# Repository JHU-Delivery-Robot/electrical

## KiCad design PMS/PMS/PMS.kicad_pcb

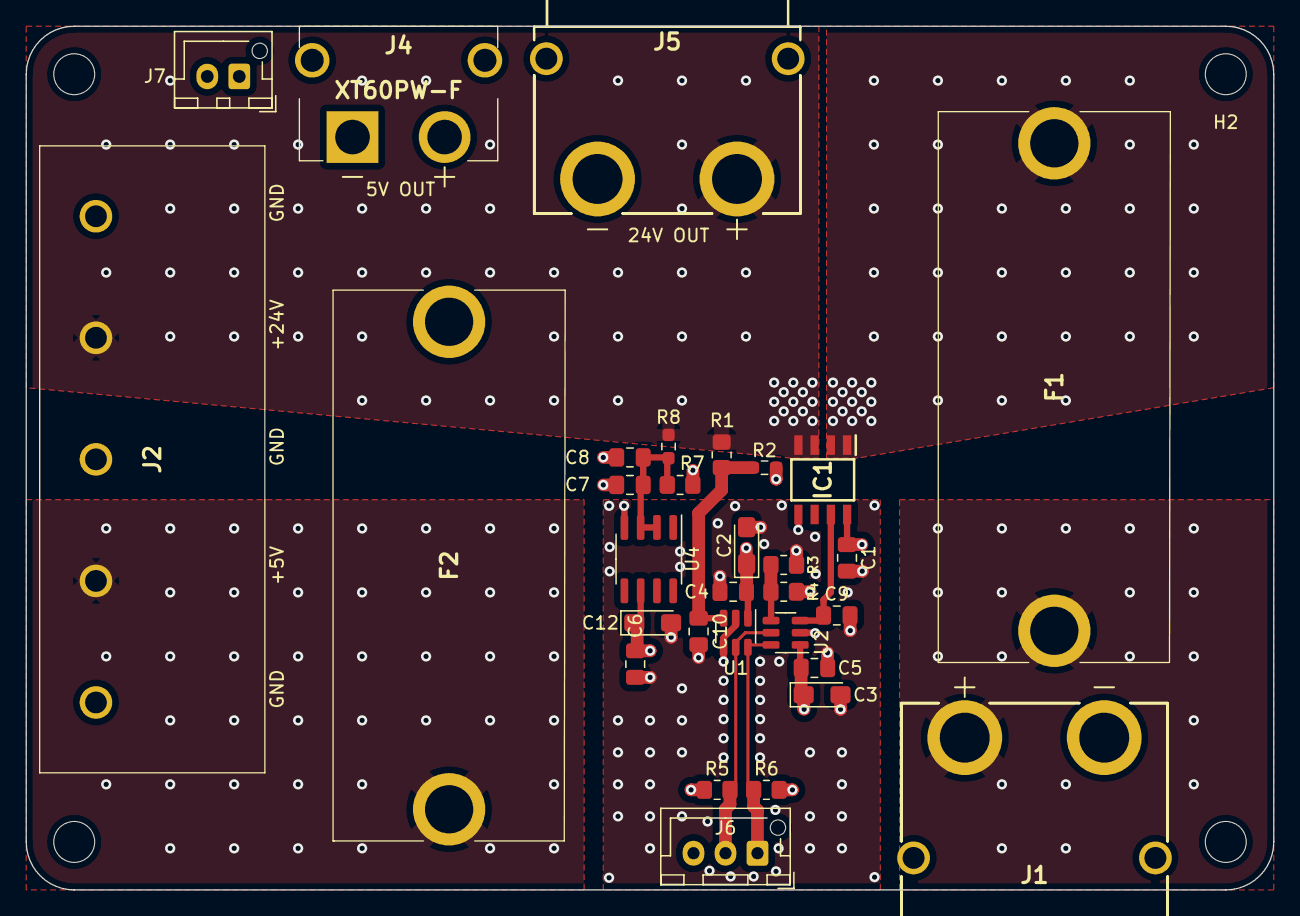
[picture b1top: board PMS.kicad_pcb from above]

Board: 4 copper layers, 97.5 x 67.5 mm, 35 parts (0 on the bottom side), 13 nets.

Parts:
C1, C4, C5, C6, C7: .1uF; C_0805_2012Metric_Pad1.18x1.45mm_HandSolder
C2, C3: 4.7uF; CP_EIA-3216-18_Kemet-A_Pad1.58x1.35mm_HandSolder
C8: 10uF; C_0805_2012Metric_Pad1.18x1.45mm_HandSolder
C9, C10: 470 pF; C_0805_2012Metric_Pad1.18x1.45mm_HandSolder
C12: 1 uF; CP_EIA-3216-18_Kemet-A_Pad1.58x1.35mm_HandSolder
F1: 30A; 3576
F2: 7.5+ A; 3576
H1, H2, H3, H4: MountingHole; MountingHole_3.2mm_M3_ISO14580
IC1: TMCS1107A1BQDRQ1; SOIC127P600X175-8N
J1: XT90PW-M; XT90PWM
J2: OSTYK44105030
J4: XT60PW-F; XT60PWF
J5: XT90PW-F
J6: Conn_01x03_Male; JST_XH_B3B-XH-AM_1x03_P2.50mm_Vertical
J7: Conn_01x02_Male; JST_XH_B2B-XH-AM_1x02_P2.50mm_Vertical
R1: 100K; R_0805_2012Metric_Pad1.20x1.40mm_HandSolder
R2: 20K; R_0603_1608Metric_Pad0.98x0.95mm_HandSolder
R3, R4: 1M; R_0805_2012Metric_Pad1.20x1.40mm_HandSolder
R5, R6: 10K; R_0805_2012Metric_Pad1.20x1.40mm_HandSolder
R7: 1.5K; R_0805_2012Metric_Pad1.20x1.40mm_HandSolder
R8: 1.5K; R_0603_1608Metric_Pad0.98x0.95mm_HandSolder
U1, U2: ADC101C027CIMK; SOT-23-6
U4: REF195; SOIC-8_3.9x4.9mm_P1.27mm

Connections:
24V_OUT: IC1.3 (IN-_1), IC1.4 (IN-_2), J2.2, J5.2 (+), R1.1, R8.2
+5V: F2.2, J4.2 (+), J7.2
+5VA: C1.1, C2.1, C3.1, C4.1, C5.1, C6.1, C12.1, IC1.8 (VS), R4.2, R5.2, R6.2, U1.1 (V_{A}), U2.1 (V_{A}), U4.6 (Vout)
+5VP: F2.1, J2.4
+24V: F1.2, IC1.1 (IN+_1), IC1.2 (IN+_2)
+BATT: F1.1, J1.2 (+)
GND: C1.2, C2.2, C3.2, C4.2, C5.2, C6.2, C7.1, C8.2, C9.2, C10.2, C12.2, IC1.5 (GND), J1.1 (-), J2.1, J2.3, J2.5, J4.1 (-), J4.3, J4.4, J5.1 (-), J7.1, R2.2, R3.2, R7.1, U1.2 (GND), U1.4 (ADDR), U2.2 (GND), U4.4 (GND)
unnamed: C7.2, C8.1, R7.2, R8.1, U4.2 (Vin), U4.3 (~Sleep)
unnamed: C9.1, IC1.7 (VOUT), U2.3 (V_{IN})
unnamed: C10.1, R1.2, R2.1, U1.3 (V_{IN})
unnamed: R3.1, R4.1, U2.4 (ADDR)
SCL: J6.2, R5.1, U1.5 (SCL), U2.5 (SCL)
SDA: J6.1, R6.1, U1.6 (SDA), U2.6 (SDA)

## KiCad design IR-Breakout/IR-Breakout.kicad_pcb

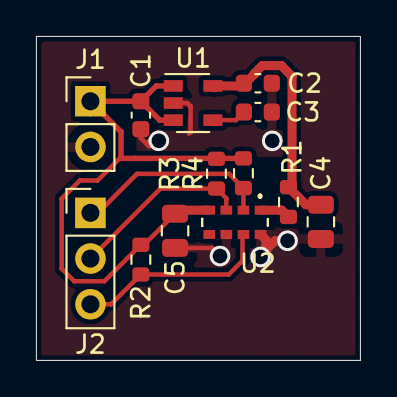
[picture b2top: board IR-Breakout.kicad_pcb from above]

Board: 2 copper layers, 18.0 x 18.0 mm, 13 parts (0 on the bottom side), 8 nets.

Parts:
C1, C2: 1u; C_0603_1608Metric
C3: 0.1u; C_0603_1608Metric
C4: 4.7u; C_0805_2012Metric
C5: 10u; C_0805_2012Metric
J1: PWR; PinHeader_1x02_P2.54mm_Vertical
J2: I2C; PinHeader_1x03_P2.54mm_Vertical
R1: 22; R_0603_1608Metric
R2, R3, R4: 10K; R_0603_1608Metric
U1: LDK120M18R; SOT-23-5
U2: TMD37253M

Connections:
+1V8: C2.1, C4.1, R1.1, U1.5 (OUT)
+3V3: C1.1, C5.1, J1.1, R2.1, R3.1, R4.1, U1.1 (IN), U1.3 (EN), U2.4 (LEDA)
/INT: J2.3, R2.2, U2.7 (INT)
/SCL: J2.2, R3.2, U2.3 (SCL)
/SDA: J2.1, R4.2, U2.2 (SDA)
GND: C1.2, C2.2, C3.2, C4.2, C5.2, J1.2, U1.2 (GND), U2.6 (PGND), U2.8 (VSS)
unnamed: C3.1, U1.4 (BP)
unnamed: R1.2, U2.1 (VDD)

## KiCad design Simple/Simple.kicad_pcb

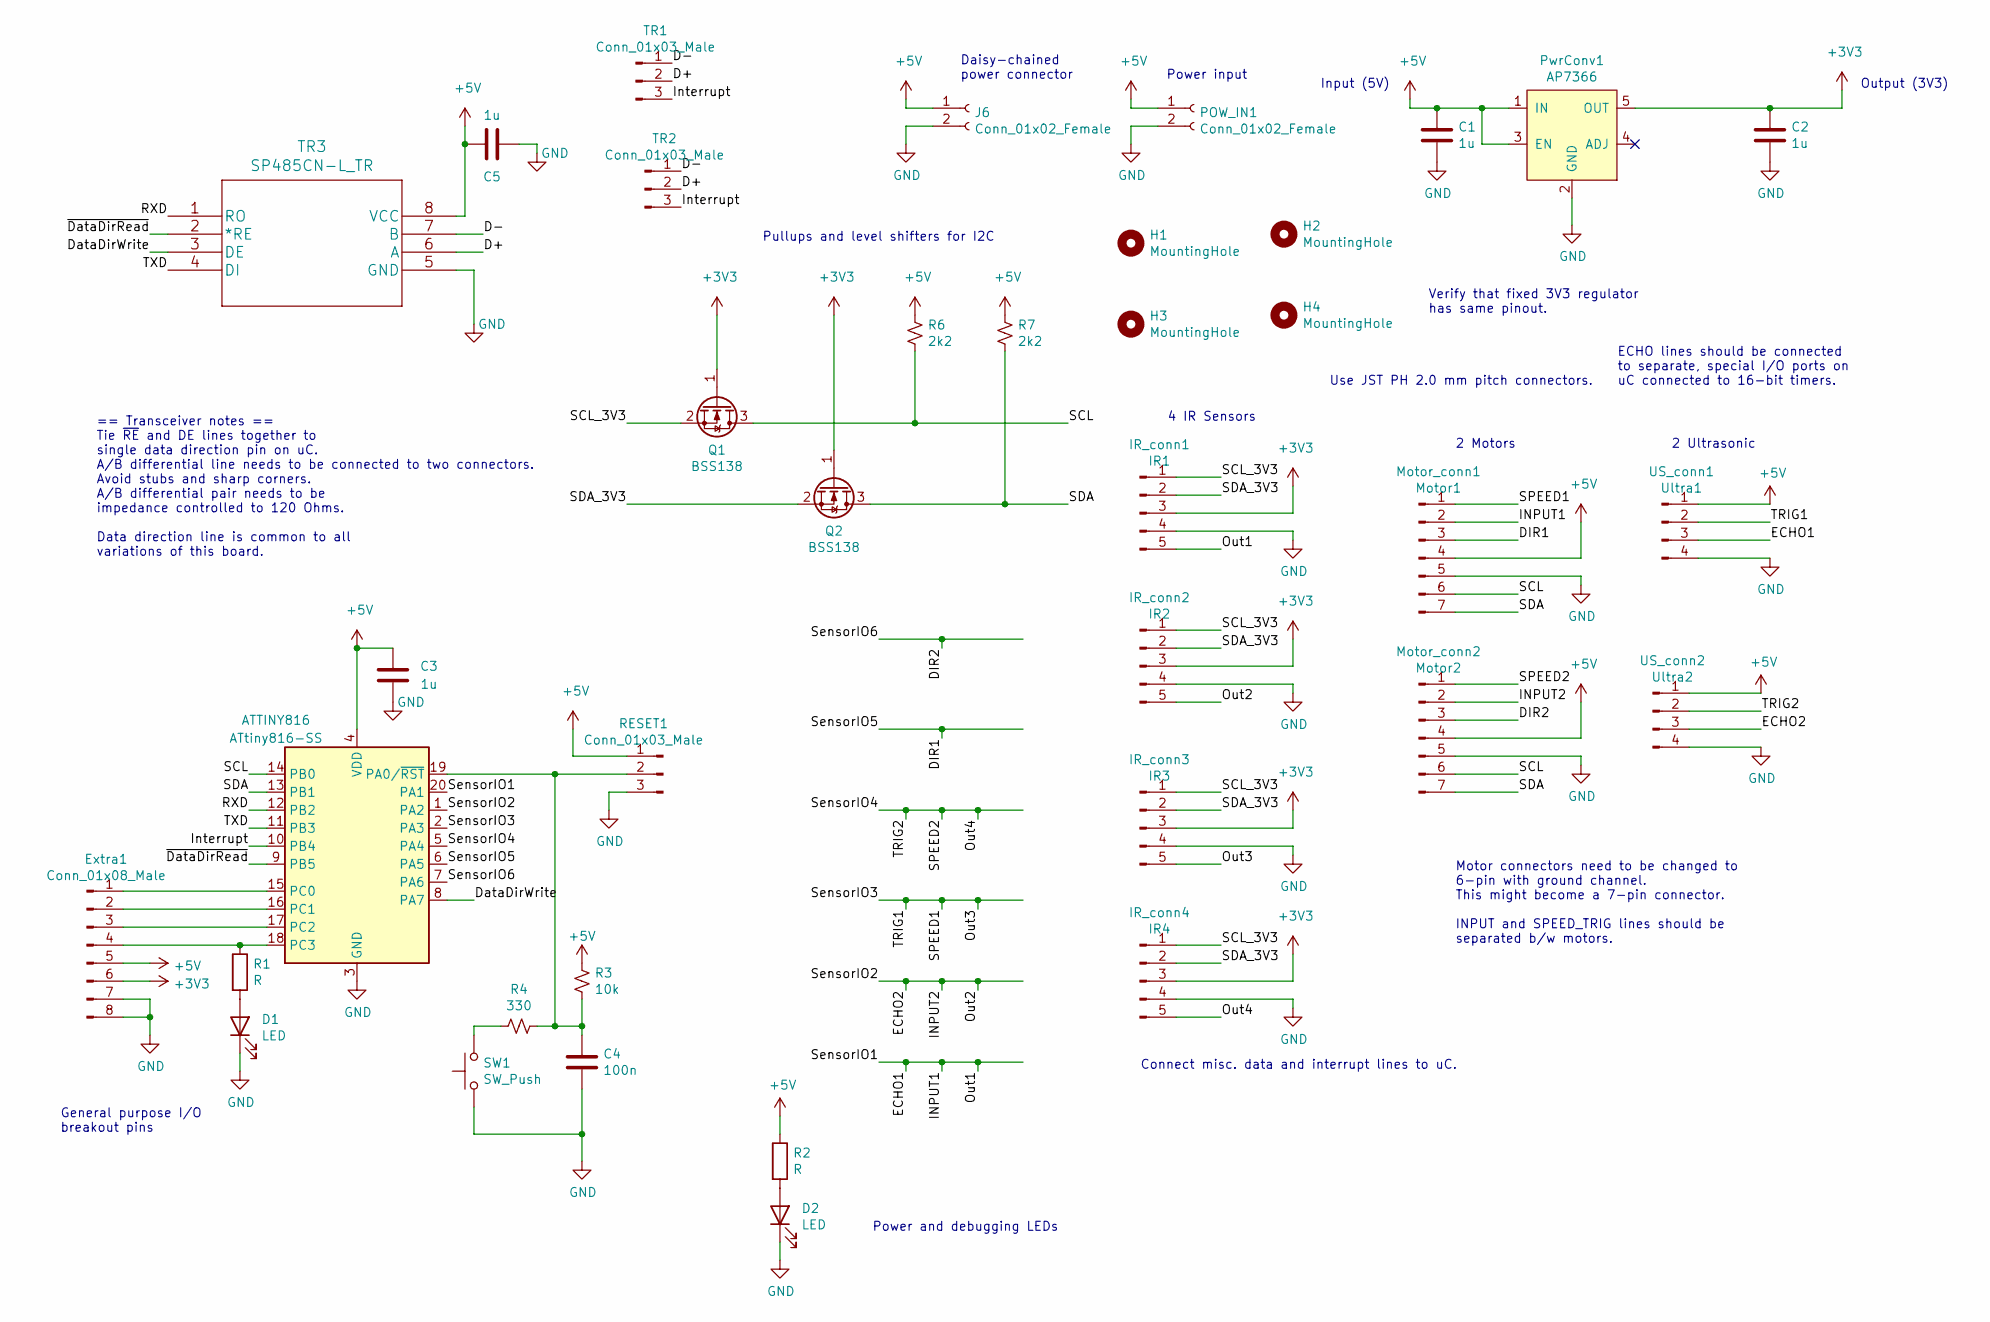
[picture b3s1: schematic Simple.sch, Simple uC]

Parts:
ATTINY816: ATtiny816-SS; SOIC-20W_7.5x12.8mm_P1.27mm
C1, C2, C3, C5: 1u; C_0603_1608Metric
C4: 100n; C_0603_1608Metric
D1, D2: LED; LED_0603_1608Metric
Extra1: Conn_01x08_Male; JST_PH_B8B-PH-K_1x08_P2.00mm_Vertical
H1, H2, H3, H4: MountingHole; MountingHole_3.2mm_M3_Pad_Via
IR_conn1: IR1; JST_PH_B5B-PH-K_1x05_P2.00mm_Vertical
IR_conn2: IR2; JST_PH_B5B-PH-K_1x05_P2.00mm_Vertical
IR_conn3: IR3; JST_PH_B5B-PH-K_1x05_P2.00mm_Vertical
IR_conn4: IR4; JST_PH_B5B-PH-K_1x05_P2.00mm_Vertical
J6: Conn_01x02_Female; JST_PH_B2B-PH-K_1x02_P2.00mm_Vertical
Motor_conn1: Motor1; JST_PH_B7B-PH-K_1x07_P2.00mm_Vertical
Motor_conn2: Motor2; JST_PH_B7B-PH-K_1x07_P2.00mm_Vertical
POW_IN1: Conn_01x02_Female; JST_PH_B2B-PH-K_1x02_P2.00mm_Vertical
PwrConv1: AP7366; SOT-23-5
Q1, Q2: BSS138; SOT-23
R1, R2: R; R_0603_1608Metric
R3: 10k; R_0603_1608Metric
R4: 330; R_0603_1608Metric
R6, R7: 2k2; R_0603_1608Metric
RESET1: Conn_01x03_Male; JST_PH_B3B-PH-K_1x03_P2.00mm_Vertical
SW1: SW_Push; SW_SPST_PTS815
TR1, TR2: Conn_01x03_Male; JST_PH_B3B-PH-K_1x03_P2.00mm_Vertical
TR3: SP485CN-L_TR; SOIC-8_3.9x4.9mm_P1.27mm
US_conn1: Ultra1; JST_PH_B4B-PH-K_1x04_P2.00mm_Vertical
US_conn2: Ultra2; JST_PH_B4B-PH-K_1x04_P2.00mm_Vertical

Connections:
+3V3: C2.1, Extra1.6, IR_conn1.3, IR_conn2.3, IR_conn3.3, IR_conn4.3, PwrConv1.5 (OUT), Q1.1 (G), Q2.1 (G)
+5V: ATTINY816.4 (VDD), C1.1, C3.1, C5.2, Extra1.5, J6.1, Motor_conn1.4, Motor_conn2.4, POW_IN1.1, PwrConv1.1 (IN), PwrConv1.3 (EN), R2.1, R3.1, R6.1, R7.1, RESET1.1, TR3.8 (VCC), US_conn1.1, US_conn2.1; also elsewhere on the board
/D+: TR1.2, TR2.2, TR3.6 (A)
/D-: TR1.1, TR2.1, TR3.7 (B)
/DIR1: ATTINY816.6 (PA5), Motor_conn1.3
/DIR2: ATTINY816.7 (PA6), Motor_conn2.3
/DataDirWrite: ATTINY816.8 (PA7), TR3.3 (DE)
/ECHO1: ATTINY816.20 (PA1), IR_conn1.5, Motor_conn1.2, US_conn1.3
/ECHO2: ATTINY816.1 (PA2), IR_conn2.5, Motor_conn2.2, US_conn2.3
/Interrupt: ATTINY816.10 (PB4), TR1.3, TR2.3
/Out3: ATTINY816.2 (PA3), IR_conn3.5, Motor_conn1.1, US_conn1.2
/Out4: ATTINY816.5 (PA4), IR_conn4.5, Motor_conn2.1, US_conn2.2
/RXD: ATTINY816.12 (PB2), TR3.1 (RO)
/SCL: ATTINY816.14 (PB0), Motor_conn1.6, Motor_conn2.6, Q1.3 (D), R6.2
/SCL_3V3: IR_conn1.1, IR_conn2.1, IR_conn3.1, IR_conn4.1, Q1.2 (S)
/SDA: ATTINY816.13 (PB1), Motor_conn1.7, Motor_conn2.7, Q2.3 (D), R7.2
/SDA_3V3: IR_conn1.2, IR_conn2.2, IR_conn3.2, IR_conn4.2, Q2.2 (S)
/TXD: ATTINY816.11 (PB3), TR3.4 (DI)
/~DataDirRead: ATTINY816.9 (PB5), TR3.2 (*RE)
GND: ATTINY816.3 (GND), C1.2, C2.2, C3.2, C4.2, C5.1, D1.1 (K), D2.1 (K), Extra1.7, Extra1.8, IR_conn1.4, IR_conn2.4, IR_conn3.4, IR_conn4.4, J6.2, Motor_conn1.5, Motor_conn2.5, POW_IN1.2, PwrConv1.2 (GND), RESET1.3, SW1.1, TR3.5 (GND), US_conn1.4, US_conn2.4; also elsewhere on the board
unnamed: ATTINY816.15 (PC0), Extra1.1
unnamed: ATTINY816.16 (PC1), Extra1.2
unnamed: ATTINY816.17 (PC2), Extra1.3
unnamed: ATTINY816.18 (PC3), Extra1.4, R1.1
unnamed: ATTINY816.19 (PA0/~RST~), C4.1, R3.2, R4.2, RESET1.2
unnamed: D1.2 (A), R1.2
unnamed: D2.2 (A), R2.2
unnamed: R4.1, SW1.2

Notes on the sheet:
2 Ultrasonic
2 Motors
4 IR Sensors
Input (5V)
Output (3V3)
Motor connectors need to be changed to 6-pin with ground channel. This might become a 7-pin connector. INPUT and SPEED_TRIG lines should be separated b/w motors.
Verify that fixed 3V3 regulator has same pinout.
ECHO lines should be connected to separate, special I/O ports on uC connected to 16-bit timers.
Use JST PH 2.0 mm pitch connectors.
Connect misc. data and interrupt lines to uC.
Pullups and level shifters for I2C
== Transceiver notes == Tie ~RE~ and DE lines together to single data direction pin on uC. A/B differential line needs to be connected to two connectors. Avoid stubs and sharp corners. A/B differential pair needs to be impedance controlled to 120 Ohms. Data direction line is common to all variation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
Power input
General purpose I/O breakout pins
Daisy-chained power connector
Power and debugging LEDs

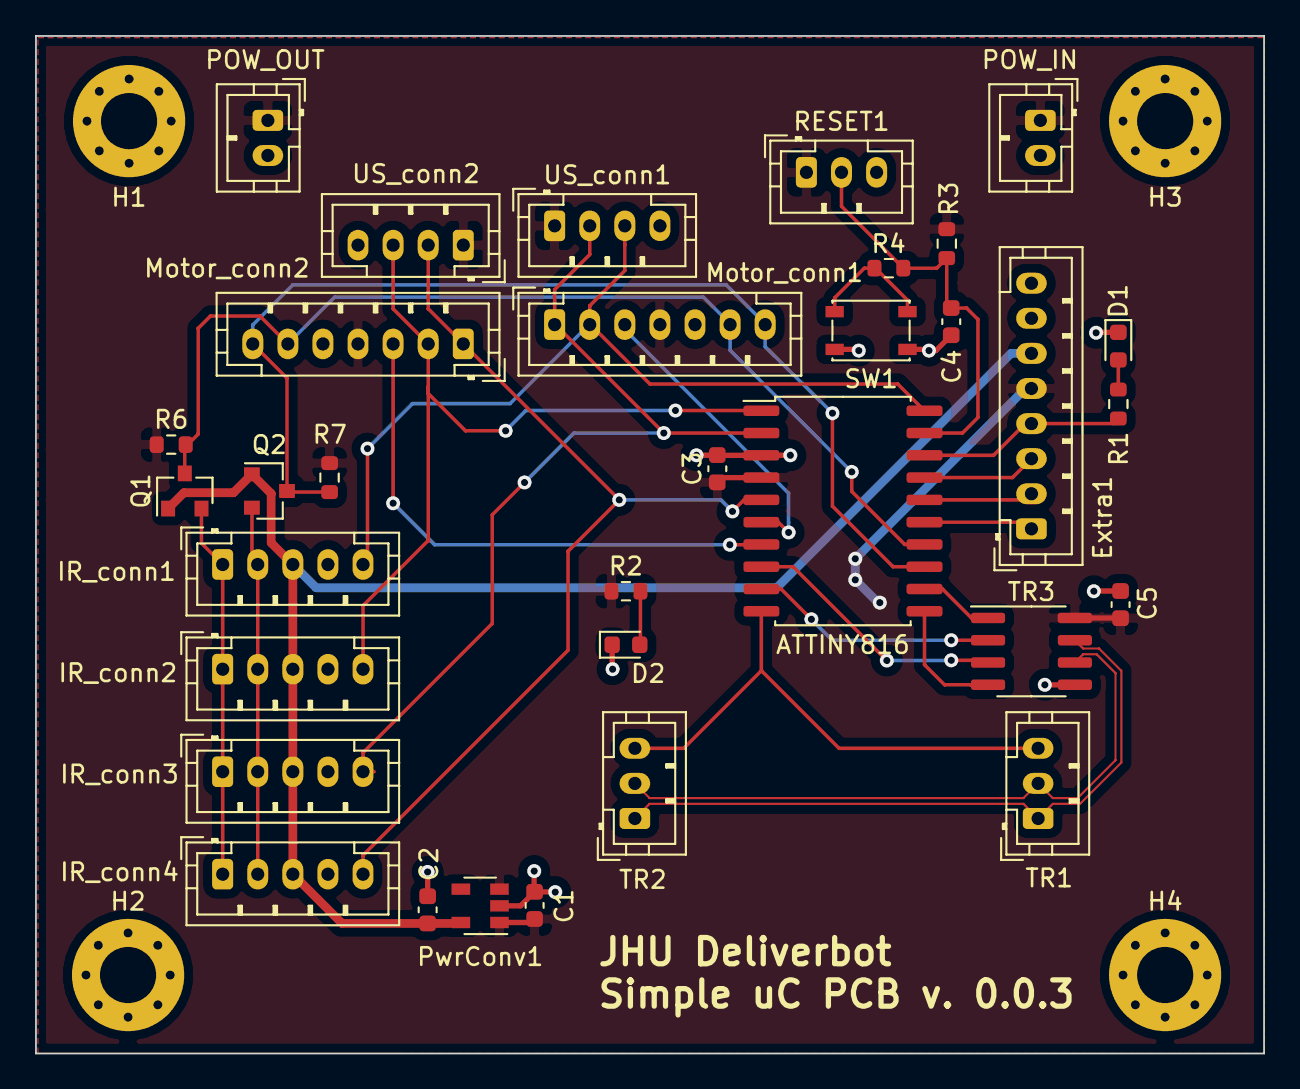
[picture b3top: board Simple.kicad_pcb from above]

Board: 4 copper layers, 70.0 x 58.0 mm, 37 parts (0 on the bottom side), 28 nets.

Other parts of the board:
POW_IN: Conn_01x02_Female; JST_PH_B2B-PH-K_1x02_P2.00mm_Vertical
POW_OUT: Conn_01x02_Female; JST_PH_B2B-PH-K_1x02_P2.00mm_Vertical

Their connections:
+5V: POW_IN.1, POW_OUT.1; also elsewhere on the board
GND: POW_IN.2, POW_OUT.2; also elsewhere on the board

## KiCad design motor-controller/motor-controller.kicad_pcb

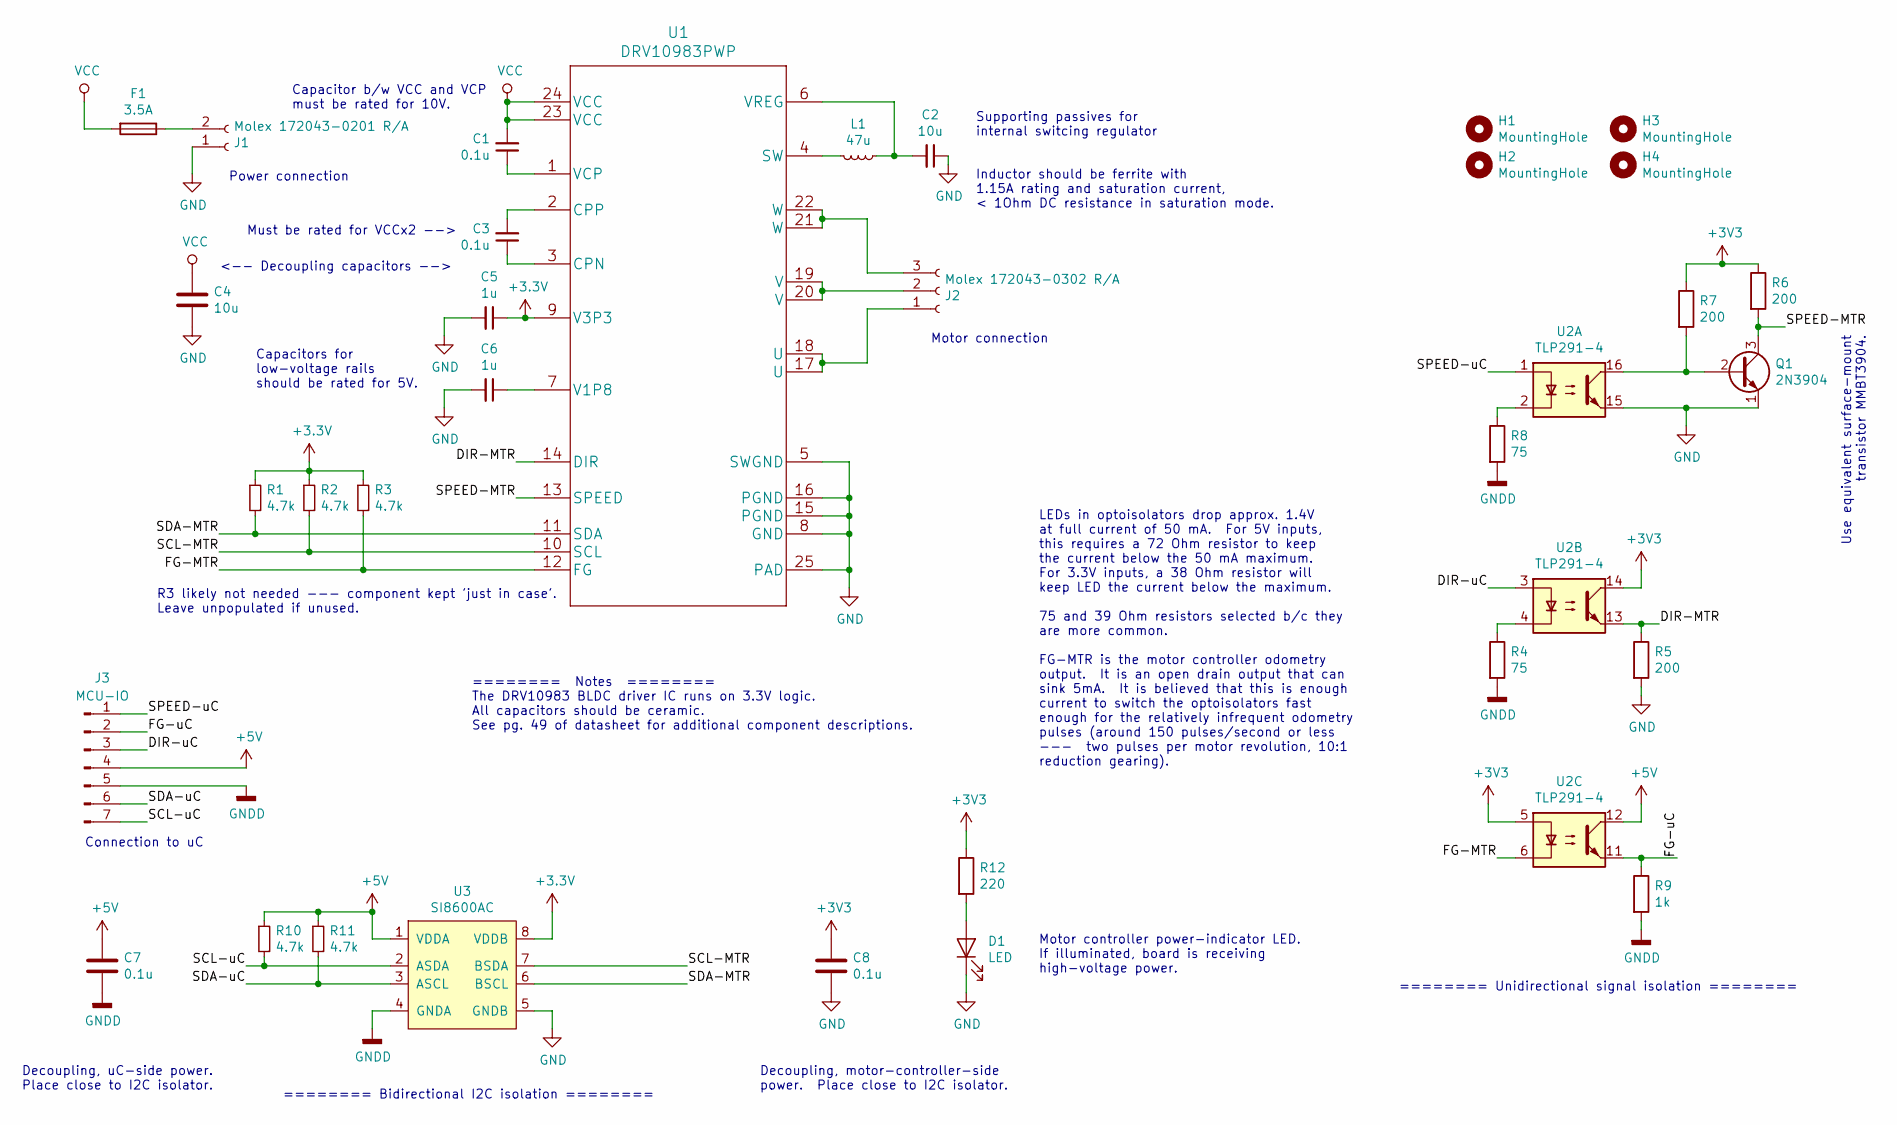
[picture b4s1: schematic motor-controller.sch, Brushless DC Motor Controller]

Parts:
C1, C3, C7, C8: 0.1u; C_0603_1608Metric
C2, C4: 10u; C_0603_1608Metric
C5, C6: 1u; C_0603_1608Metric
D1: LED; LED_0603_1608Metric
F1: 3.5A; littelfuse-01110505Z-5x15mm
H1, H2, H3, H4: MountingHole; MountingHole_3.2mm_M3
J1: Molex 172043-0201 R/A; CONN_1720430201_MOL; Digi-Key part number WM20737-ND
J2: Molex 172043-0302 R/A; 172043-0302_MOL; Digi-Key part number WM20740-ND
J3: MCU-IO; JST_XH_B07B-XH-A_1x07_P2.50mm_Vertical; Digi-Key part number 455-2252-ND
L1: 47u; L_Taiyo-Yuden_NR-60xx; Digi-Key part number 587-2956-6-ND
Q1: 2N3904; SOT-23
R1, R2, R3, R10, R11: 4.7k; R_0603_1608Metric
R4, R8: 75; R_0603_1608Metric
R5, R6, R7: 200; R_0603_1608Metric
R9: 1k; R_0603_1608Metric
R12: 220; R_0603_1608Metric
U1: DRV10983PWP; PWP0024B
U2: TLP291-4; SOIC-16_4.55x10.3mm_P1.27mm
U3: SI8600AC; SOIC-8_3.9x4.9mm_P1.27mm

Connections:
+5V: C7.1, J3.4, R10.1, R11.1, U2.12, U3.1 (VDDA)
/DIR-MTR: R5.1, U1.14 (DIR), U2.13
/DIR-uC: J3.3, U2.3
/FG-MTR: R3.2, U1.12 (FG), U2.6
/FG-uC: J3.2, R9.1, U2.11
/SCL-MTR: R2.2, U1.10 (SCL), U3.7 (BSDA)
/SCL-uC: J3.7, R10.2, U3.2 (ASDA)
/SDA-MTR: R1.2, U1.11 (SDA), U3.6 (BSCL)
/SDA-uC: J3.6, R11.2, U3.3 (ASCL)
/SPEED-MTR: Q1.3 (C), R6.2, U1.13 (SPEED)
/SPEED-uC: J3.1, U2.1
GND: C2.1, C4.2, C5.2, C6.2, C8.2, D1.1 (K), J1.1, Q1.1 (E), R5.2, U1.5 (SWGND), U1.8 (GND), U1.15 (PGND), U1.16 (PGND), U1.25 (PAD), U2.15, U3.5 (GNDB)
GNDD: C7.2, J3.5, R4.2, R8.2, R9.2, U3.4 (GNDA)
unnamed: C1.1, U1.1 (VCP)
unnamed: C2.2, L1.1, U1.6 (VREG)
unnamed: C3.1, U1.3 (CPN)
unnamed: C3.2, U1.2 (CPP)
unnamed: C6.1, U1.7 (V1P8)
unnamed: D1.2 (A), R12.2
unnamed: F1.1, J1.2
unnamed: J2.1, U1.17 (U), U1.18 (U)
unnamed: J2.2, U1.19 (V), U1.20 (V)
unnamed: J2.3, U1.21 (W), U1.22 (W)
unnamed: L1.2, U1.4 (SW)
unnamed: Q1.2 (B), R7.2, U2.16
unnamed: R4.1, U2.4
unnamed: R8.1, U2.2
VCC: C1.2, C4.1, F1.2, U1.23 (VCC), U1.24 (VCC)

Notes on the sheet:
Motor connection
Power connection
<-- Decoupling capacitors -->
Supporting passives for internal switcing regulator
Connection to uC
Capacitor b/w VCC and VCP must be rated for 10V.
Capacitors for low-voltage rails should be rated for 5V.
Must be rated for VCCx2 -->
======== Notes ======== The DRV10983 BLDC driver IC runs on 3.3V logic. All capacitors should be ceramic. See pg. 49 of datasheet for additional component descriptions.
Inductor should be ferrite with 1.15A rating and saturation current, < 1Ohm DC resistance in saturation mode.
Decoupling, uC-side power. Place close to I2C isolator.
LEDs in optoisolators drop approx. 1.4V at full current of 50 mA. For 5V inputs, this requires a 72 Ohm resistor to keep the current below the 50 mA maximum. For 3.3V inputs, a 38 Ohm resistor will keep LED the current below the maximum. 75 and 39 Ohm resistors selected b/c they are more common. FG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
======== Unidirectional signal isolation ========
======== Bidirectional I2C isolation ========
Use equivalent surface-mount transistor MMBT3904.
R3 likely not needed --- component kept 'just in case'. Leave unpopulated if unused.
Decoupling, motor-controller-side power. Place close to I2C isolator.
Motor controller power-indicator LED. If illuminated, board is receiving high-voltage power.

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
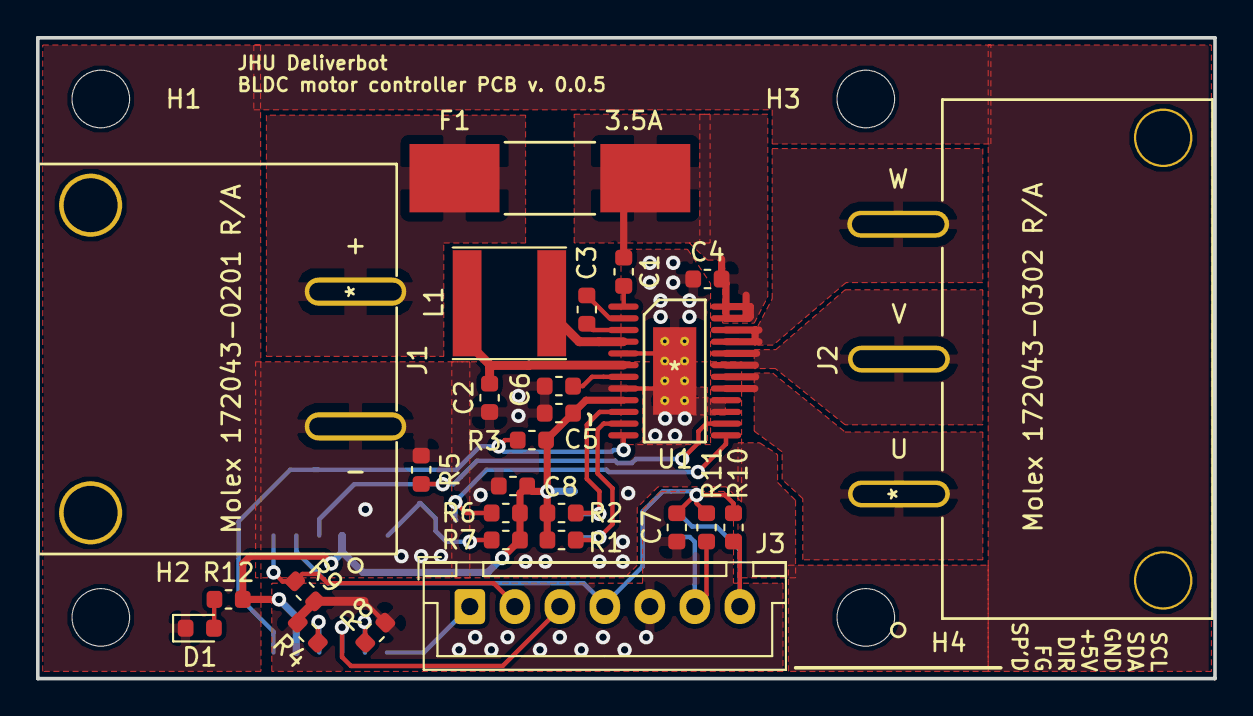
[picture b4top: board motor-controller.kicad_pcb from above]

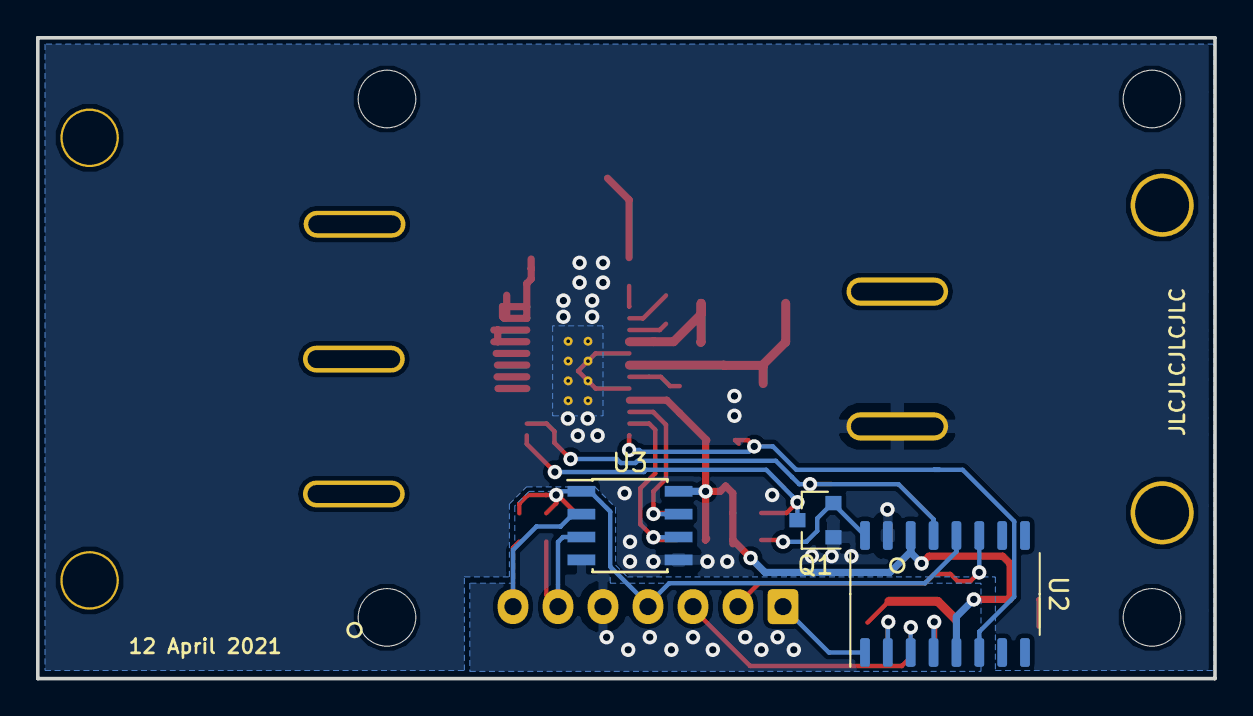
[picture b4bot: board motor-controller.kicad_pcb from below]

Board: 2 copper layers, 65.4 x 35.6 mm, 34 parts (3 on the bottom side), 29 nets.

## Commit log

2020-12-30 Added BLDC motorcontroller IC PCB
2020-12-30 Added ground planes, thermal vias
2020-12-30 Added back top edge cut
2021-01-12 Added fuse holder and modified position of mounting holes
2021-01-14 Adjusted copper pours; reroute I2C and other digital signal traces
2021-01-17 Thermal vias connected to pad in driver IC footprint; added PCB dimensions, adjusted fuse pours.
2021-02-08 Added current simple uC pcb schematic for review
2021-02-12 Added notes for things to do on simple uC schematic.
2021-02-22 transceiver added, along with adressing commented changes in schematic
2021-03-06 SimpleUC: Update to ATTINY816
    Updated symbol and schematic to use the larger version of the chip since
    we ran out of pins.
2021-03-12 Added schematic symbol for SI86000 isolator
2021-03-19 Added interrupt connection to uC
2021-03-19 Added isolation for digital signals going offboard to schematic.
2021-03-19 Prelayout checkout modifications. Version pushed to 0.0.3.
    Added indicator LEDs, broke out unused pins and extra power pins,
    separated data direction pin into two pins --- one for read, one
    for write.
2021-03-24 Optoisolation modifications and pre-layout changes.
    Added NPN to optoisolator output of PWM input signal for faster switching.
    Set resistor values on optoisolator output for non-open-collector signals
    to 200 ohms. Added back pullup resistor to odometry output just in case;
    the footprint should remain unpopulated unless there is a misunderstanding
    for how the odometry output works.
2021-03-26 Prelayout modifications; changed 7-pin connector pinout to permit tighter layout.
2021-03-28 Added in isolator traces and placed resistors; need to add ground planes and tweak layout.
2021-03-30 Added in uC-side ground planes; adjusted isolator trace layouts to pass DRC
2021-04-02 Layout started and sensor connectors are connected to eachother but not microcontroller
2021-04-05 Added more traces between uC and Transceiver
2021-04-08 rotated motor/ultrasonic connectors and added traces for all but pwr, gnd, d+/-
2021-04-12 Preparation for fabrication. Changed PCB silkscreen and added part numbers to schematic.
    Added board description, version number, and date to PCB silkscreen.
    Added Digi-Key part numbers and mating connectors as symbol attributes
    for some connectors in schematic.
2021-04-13 Adjusted silkscreen text size.
    Enlargened size of all silkscreen text smaller than 0.8mmx0.8mm 0.15mm
    thickness to those dimensions, which are the minimum legible silkscreen
    resolution offered by JLCPCB's process.
2021-04-16 minor routing changes and added pwr and gnd planes
2021-04-16 added mounting holes and moved vias away from pads
2021-04-23 Rerouted 3V3 trace and fixed borders of planes
2021-04-24 fixed outline's right angles and moved silk lettering
2021-05-16 Modifications from review of PCB.
    - Aligned connector and hole footprints
    - Shifted positions of some bits of silkscreen text
    - Redrew 3V3 connection to utility connection
    - Added 5V connection on backplane to microcontroller
    - Added PCB version and manufacturer serial number silkscreen text
2021-06-17 Rerouted differential pair traces with dimensions for 120 ohm diff. imped.
    Diff. trace width changed to 0.126238 mm (4.97 mil); separation changed to
    0.2032 mm (8 mil). Min. trace width in global design rules changed to
    0.09 mm (3.5 mil), which is JLCPCB's min. trace width for traces on the
    **outer layer** of 1 oz Cu. 4- or 6-layer boards. (Note that min. trace
    width for inner layers is still 0.127 mm (5 mil).
2021-06-17 Added note to Dwgs.User layer in PCB indicating which JLCPCB stackup to use to get proper 120-ohm diff. imped. control.
2021-07-03 Added silkscreen + bottom layer soldermask to simple uC PCB
2021-09-12 Add IR Breakout PCB
    Note: This PCB is designed to be fabricated on the PCB mill.
2022-02-15 Adding PMS. Pending review
2022-02-15 several changes to satisfy ERC
2022-02-23 Updated PMS. Now includes option for LA12 with other fixes.
2022-02-24 annotated schematic
2022-02-25 added reverse polarity protection
2022-02-25 cleanup and now ERC compliant
2022-02-25 switched to the correct zener diode
2022-03-03 Associated footprints to components
2022-03-06 adding BOM PMS.csv
2022-03-07 Layout complete.
2022-03-07 cleanup
2022-03-07 all traces now routed on the topmost layer
2022-03-08 moved silkscreen
2022-03-15 Changed regulator and updated layout. No longer includes LA12.
2022-03-15 updates to satisfy DRC
2022-03-16 changed solder jumper footprint and added silk labels for XT60 connectors
2022-03-18 changed to XT90s for 24V
2022-03-20 Changed to barrier strip for connection to Mean-Well. Interconnects cannot be erroneously connected
2022-03-23 Adding updated BOM
2022-04-11 updated PMS. Resistor values chosen for accurate current. ADC layouts altered to add via fence and reduce EMI. ADC input low-pass capacitors added.
2022-04-12 minor changes
2022-04-12 changed star ground
2022-04-12 More changes to grounding
2022-04-19 corrected values for pullups on SDA, SCL, and INT
2022-04-25 increased distance between planes. Improved top GND plane for analog portion of board. simplified some geometries. VIAS.
2022-04-27 HOLY MOLY! Adding many, many vias for thermals and for EMI. Fencing spacing was altered to max wavelength / 40.
2022-04-30 adding updated measurements for PMS

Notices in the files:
parts and their libraries:
Copyright 2016 Accelerated Designs. All rights reserved.
